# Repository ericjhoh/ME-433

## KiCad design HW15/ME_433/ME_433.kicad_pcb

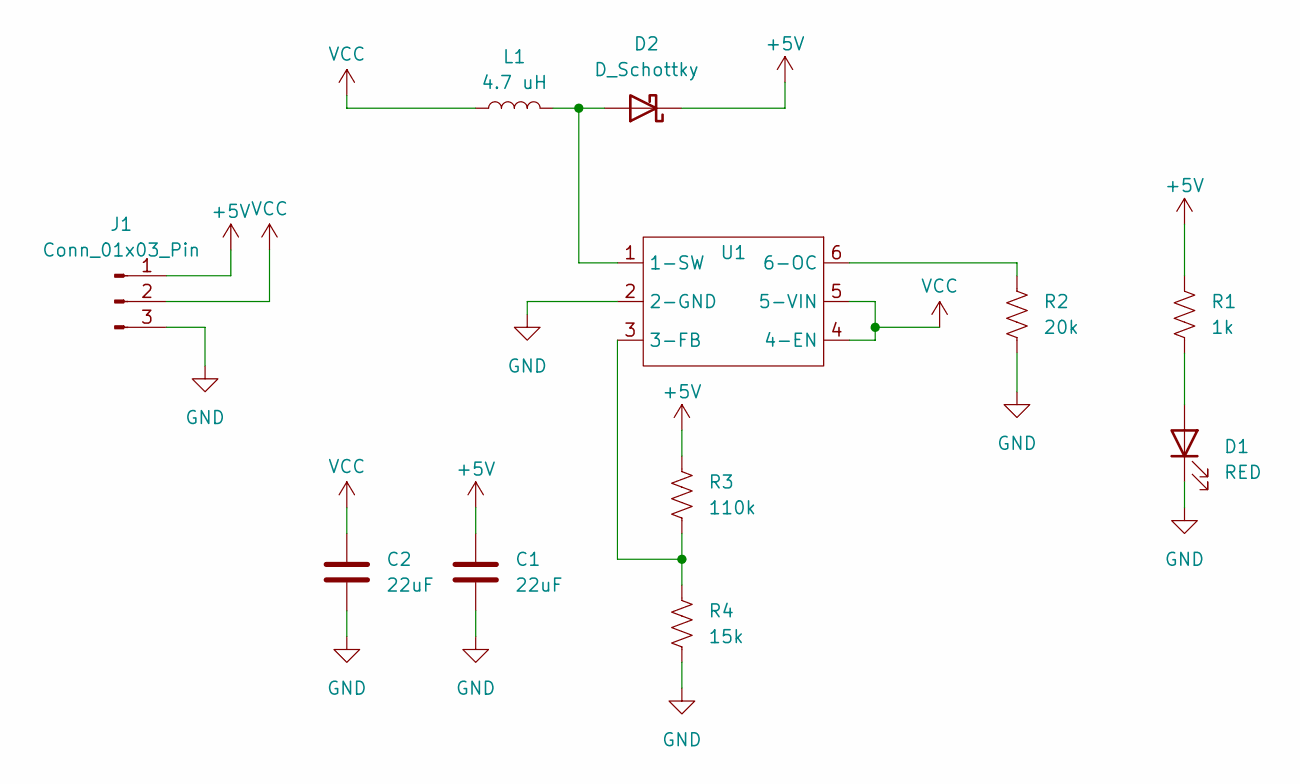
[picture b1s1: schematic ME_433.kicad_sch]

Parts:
C1, C2: 22uF; C_0805_2012Metric
D1: RED; LED_0805_2012Metric
D2: D_Schottky; D_SOD-123
J1: Conn_01x03_Pin; PinHeader_1x03_P2.54mm_Vertical
L1: 4.7 uH; L_0805_2012Metric
R1: 1k; R_0805_2012Metric
R2: 20k; R_0805_2012Metric
R3: 110k; R_0805_2012Metric
R4: 15k; R_0805_2012Metric
U1: SOT-23-6

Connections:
+5V: C1.1, D2.1 (K), J1.1, R1.1, R3.1
GND: C1.2, C2.2, D1.1 (K), J1.3, R2.2, R4.2, U1.2 (2-GND)
unnamed: D1.2 (A), R1.2
unnamed: D2.2 (A), L1.2, U1.1 (1-SW)
unnamed: R3.2, R4.1, U1.3 (3-FB)
unnamed: R2.1, U1.6 (6-OC)
VCC: C2.1, J1.2, L1.1, U1.4 (4-EN), U1.5 (5-VIN)

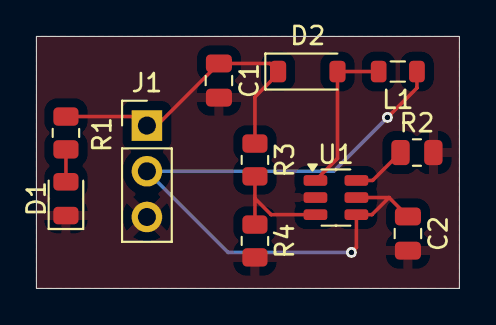
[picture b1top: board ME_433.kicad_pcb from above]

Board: 2 copper layers, 23.5 x 14.0 mm, 11 parts (0 on the bottom side), 7 nets.

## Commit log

2025-04-09 Created the Example Projects
    Used the Pico Extension on Vs code to create example projects
2025-04-09 Made the functionality of Toggling an LED with a button
    Added the code to toggle the LED with a button and displayed the number of presses onto the putty terminal
2025-04-15 HW3
    Finished
2025-04-18 Able to create a certain anallaog voltage from a digital
    Created SPI writing function. Need to create sine and triangle wave now
2025-04-18 Created Triangle and Sine Wave
    Finished HW4
2025-04-18 Did first part of HW5 timer of math functions
2025-04-18 Finished HW5
    Finish HW5
2025-04-23 HW6
    finsihed HW6
2025-04-25 HW7
    finsihed HW7 OLED with I2C comm
2025-04-29 Finished HW 8
2025-05-03 HW9 finish
2025-05-05 HW10 finish
2025-05-07 set up HW11
2025-05-12 finished hw 11
2025-05-26 HW 13
2025-05-28 pushing hw 13 and 15
    clean up push
2025-05-30 wheel cad start
2025-05-30 finished wheel
2025-05-31 Design Rough Draft
2025-05-31 created slicer files
2025-05-31 updated wheel
2025-06-01 hopefully final print
2025-06-01 opened solidworks random push needed
2025-06-01 FINAL FINAL DESIGN
2025-06-02 HW12
    finish
2025-06-03 HW 16 finish and HW 17 start
2025-06-04 Made arbitrary proportional gains for final car
2025-06-04 added start button and editing the gains
    maybe I will add another COM line above the middle
2025-06-04 Edited Final Gains
    Robot final gains only used the middle center of mass. Had to make it turn more extremely when the offset was large.
2025-06-06 Uploaded final
